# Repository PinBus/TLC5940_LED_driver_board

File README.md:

# TLC5940 LED Driver Board - Rev. 1.0

This is a board designed for a TLC5940 LED driver IC. Each of the TLC5940's outputs has a separate connector. It can be used with the [1206 LED Satellite Board](https://github.com/PinBus/1206_LED_satellite_board).

The values of the parts listed in the BOM are chosen based on V<sub>CC</sub> = +5V, V<sub>O</sub> = +12V, and I<sub>OLC</sub> = 30mA. If you want another value for I<sub>OLC</sub>, change the value of resistor R1 using the formula given on page 17 of the [datasheet](assets/tlc5940.pdf).

When using another voltage for V<sub>CC</sub> or when using another colour of LED, remember to change the value of R2. Whe using another voltage for V<sub>O</sub> or using another colour of LED, remember to change the value of R3.

**Warning: These designs are made as part of a hobby project and thus come with no guarantees. Do not use these designs in for any critical systems! Working with voltages higher than +40V can be potentially dangerous, please take appropriate safety measures!**

## BOM

| Identifiers | Quantity | Part |
| ----------- | -------- | ---- |
| C1          |       1x | 100nF Ceramic capacitor, 5mm pin pitch |
| C2          |       1x | 1μF Electrolytic capacitor, 2mm pin pitch, 5mm diameter |
| D1, D2      |       2x | 3mm red LED |
| J0 - J15    |      16x | JST XH connector, 2.5mm pitch, 2-way, through-hole |
| J16         |       1x | Dupont male connector, 2.54mm pitch, 3-way, through-hole |
|             |       1x | Jumper (for the dupont connector) |
| J17, J18    |       2x | JST XH connector, 2.5mm pitch, 6-way, through-hole |
| J20         |       1x | CH 3.96 connector, 3-way, through hole |
| R1          |       1x | 1.3KΩ 0.25W resistor |
| R2          |       1x | 180Ω 0.25W resistor |
| R3          |       1x | 560Ω 0.25W resistor |
| U1          |       1x | TLC5940NT LED driver IC |
|             |       1x | Optional: Socket for the TLC5940 |

## Pictures

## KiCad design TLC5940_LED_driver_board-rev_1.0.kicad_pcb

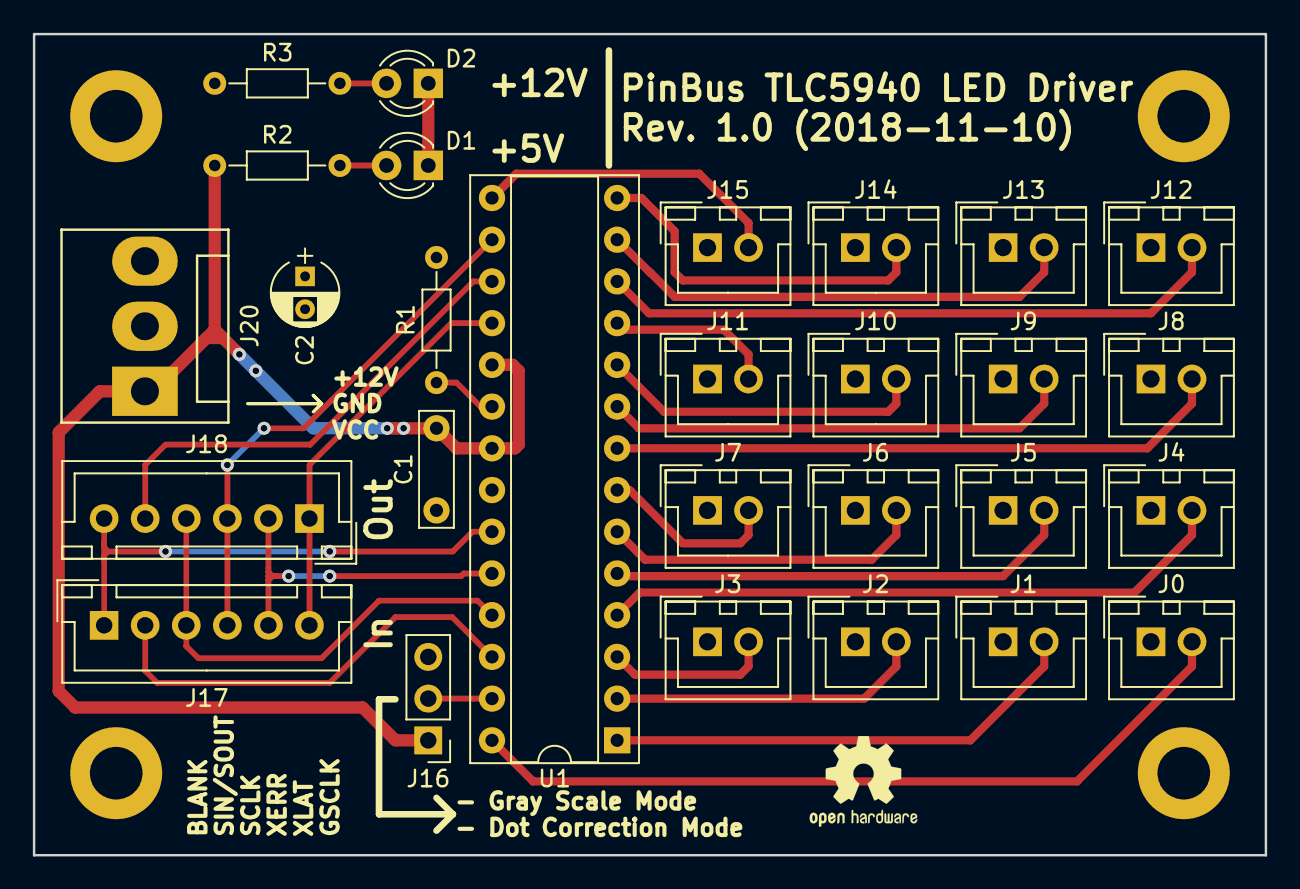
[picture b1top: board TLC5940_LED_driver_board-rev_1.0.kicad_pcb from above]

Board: 2 copper layers, 75.0 x 50.0 mm, 28 parts (0 on the bottom side), 30 nets.

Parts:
C1: 100nF; C_Rect_L7.0mm_W2.0mm_P5.00mm
C2: 1uF; CP_Radial_D4.0mm_P2.00mm
D1, D2: LED; LED_D3.0mm
J0, J1, J2, J3, J4, J5, J6, J7, J8, J9, J10, J11, J12, J13, J14, J15: Conn_01x02_Male; JST_XH_B02B-XH-A_02x2.50mm_Straight
J16: Conn_01x03_Male; Socket_Strip_Straight_1x03_Pitch2.54mm
J17, J18: Conn_01x06_Male; JST_XH_B06B-XH-A_06x2.50mm_Straight
J20: Conn_01x03_Male; Molex_KK-41791-03_03x3.96mm_Straight
R1: 1.3K; R_Axial_DIN0204_L3.6mm_D1.6mm_P7.62mm_Horizontal
R2: 180; R_Axial_DIN0204_L3.6mm_D1.6mm_P7.62mm_Horizontal
R3: 560; R_Axial_DIN0204_L3.6mm_D1.6mm_P7.62mm_Horizontal
U1: TLC5940NT; DIP-28_W7.62mm_Socket

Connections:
+12V: C2.1, J0.1, J1.1, J2.1, J3.1, J4.1, J5.1, J6.1, J7.1, J8.1, J9.1, J10.1, J11.1, J12.1, J13.1, J14.1, J15.1, J20.3, R3.1
GND: C1.2, C2.2, D1.1, D2.1, J16.3, J20.2, R1.2, U1.22
unnamed: D1.2, R2.2
unnamed: D2.2, R3.2
unnamed: J0.2, U1.28
unnamed: J1.2, U1.1
unnamed: J2.2, U1.2
unnamed: J3.2, U1.3
unnamed: J4.2, U1.4
unnamed: J5.2, U1.5
unnamed: J6.2, U1.6
unnamed: J7.2, U1.7
unnamed: J8.2, U1.8
unnamed: J9.2, U1.9
unnamed: J10.2, U1.10
unnamed: J11.2, U1.11
unnamed: J12.2, U1.12
unnamed: J13.2, U1.13
unnamed: J14.2, U1.14
unnamed: J15.2, U1.15
unnamed: J16.2, U1.27
unnamed: J17.1, J18.6, U1.23
unnamed: J17.2, U1.26
unnamed: J17.3, J18.4, U1.25
unnamed: J17.4, J18.3, U1.16
unnamed: J17.5, J18.2, U1.24
unnamed: J17.6, J18.1, U1.18
unnamed: J18.5, U1.17
unnamed: R1.1, U1.20
VCC: C1.1, J16.1, J20.1, R2.1, U1.19, U1.21

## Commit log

2018-12-11 Add hardware design files
2019-01-17 Improve documentation
